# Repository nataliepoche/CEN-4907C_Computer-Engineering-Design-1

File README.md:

# CpE Capstone, Design 1

In this repo you will find all information needed to complete labs and milestones for CpE Design 1.

**Note:** Labs are milestone are being revised this term and therefore are not immediately available.

## Using this repo

We suggest cloning this repo (`git clone https://github.com/uf-cpe-capstone/cen4907c-student-materials.git`) and pulling (`git pull`) periodically to get the latest changes (newly released labs, milestone, etc.).

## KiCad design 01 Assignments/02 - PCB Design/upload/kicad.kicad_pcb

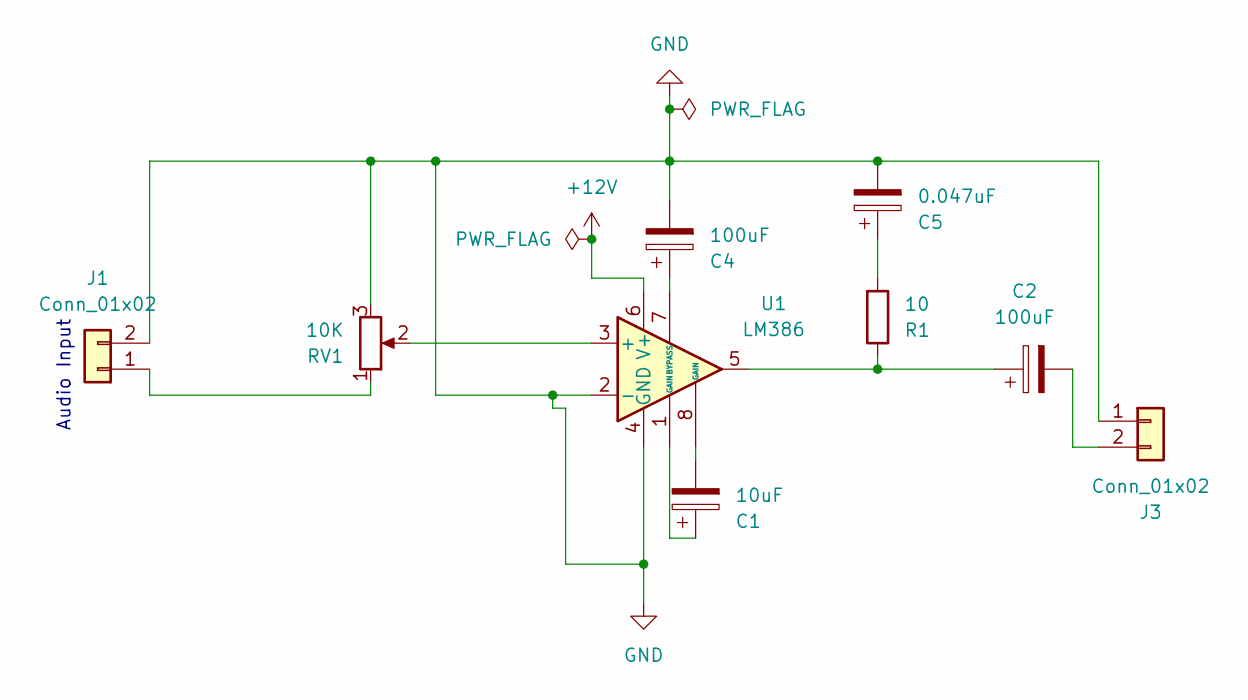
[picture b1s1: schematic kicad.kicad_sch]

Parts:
C1: 10uF; CP_Radial_D5.0mm_P2.50mm
C2, C4: 100uF; CP_Radial_D5.0mm_P2.50mm
C5: 0.047uF; CP_Radial_D5.0mm_P2.50mm
J1, J3: Conn_01x02; PinHeader_1x02_P2.54mm_Vertical
R1: 10; R_Axial_DIN0204_L3.6mm_D1.6mm_P2.54mm_Vertical
RV1: 10K; Potentiometer_Bourns_3386P_Vertical
U1: LM386; DIP-8-16_W7.62mm

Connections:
+12V: U1.6 (V+)
GND: C4.2, C5.2, J1.2, J3.1, RV1.3, U1.2 (-), U1.4 (GND)
unnamed: C1.1, U1.1 (GAIN)
unnamed: C1.2, U1.8 (GAIN)
unnamed: C2.1, R1.1, U1.5
unnamed: C5.1, R1.2
unnamed: J1.1, RV1.1
unnamed: C2.2, J3.2
unnamed: RV1.2, U1.3 (+)
unnamed: C4.1, U1.7 (BYPASS)

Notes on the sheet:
Audio Input

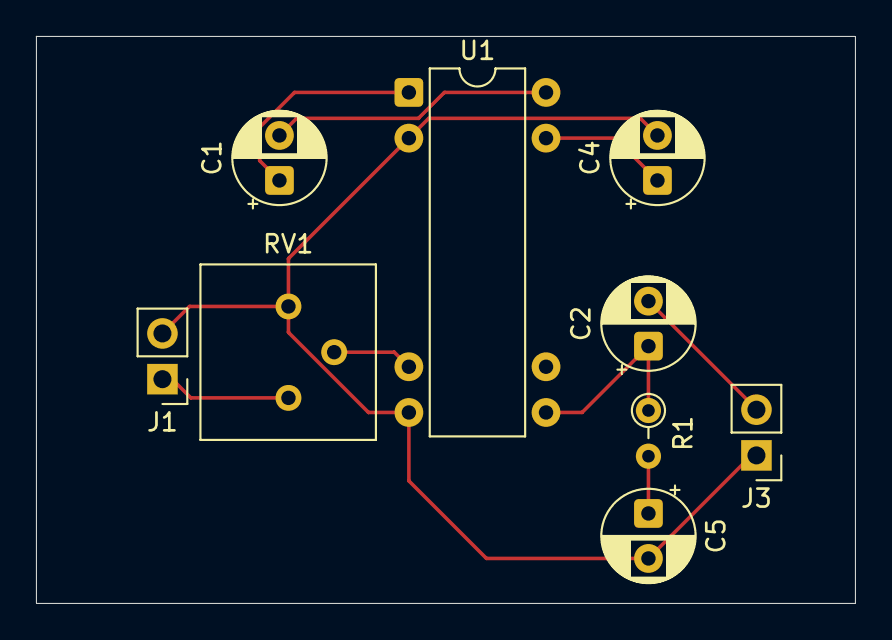
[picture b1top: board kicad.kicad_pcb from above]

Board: 2 copper layers, 45.5 x 31.5 mm, 9 parts (0 on the bottom side), 9 nets.

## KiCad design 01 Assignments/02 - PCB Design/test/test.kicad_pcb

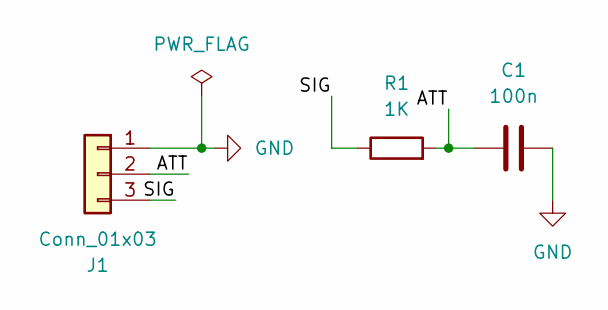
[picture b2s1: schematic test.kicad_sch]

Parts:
C1: 100n; C_0402_1005Metric_Pad0.74x0.62mm_HandSolder
J1: Conn_01x03; PinSocket_1x03_P2.54mm_Vertical
R1: 1K; R_Axial_DIN0204_L3.6mm_D1.6mm_P2.54mm_Vertical

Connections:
/ATT: C1.1, J1.2, R1.2
/SIG: J1.3, R1.1
GND: C1.2, J1.1

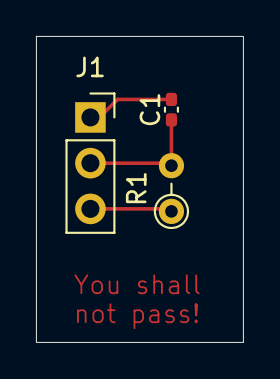
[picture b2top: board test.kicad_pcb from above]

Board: 2 copper layers, 11.5 x 17.0 mm, 3 parts (0 on the bottom side), 3 nets.
